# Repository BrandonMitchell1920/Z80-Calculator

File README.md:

# Z80 Calculator

This is a simple Z80 based calculator.  I have been doing various electronics projects
designed by other people and wanted to try making my own.  I figured a calculator
using the Z80 microprocessor would be a good choice as I had several of them on
hand and could reference other projects if needed.

## Features

The Z80 Caclulator has:

* 8K of RAM
* 8K of ROM
* 2 8-bit inputs (DIP switches)
* 6 push buttons
* Program select switch (software controlled)
* 4 seven segment displays (16-bit output)
* Expansion header for additional RAM or devices
* Blinkenlights!
* 555 timer for variable clock rate (useful for debugging)

Pretty basic, but this was more a learning exercise than anything.  Of the 8K ROM,
only a couple hundred bytes are used.  Combined with the program select switch,
it should be possible to load it up with three other programs.

The answers are displayed in hexadecimal so all operations on two eight bit numbers
would fit on the display.  The following operations are supported:

* Addition
* Subtraction
* Multiplication
* Division
* Greatest common denominator
* Square root

Only integer operations are supported, so division and square root are truncated.

## Programming

The Z80 Calculator has the following memory map:

* ROM: 0x0000 - 0x1FFF
* RAM: 0x2000 - 0x3FFF
* Unused: 0x4000 - 0xFFFF

I/O addresses are the following:

* 7SEG 1: 0x00
* 7SEG 2: 0x01
* 7SEG 3: 0x02
* 7SEG 4: 0x03
* Buttons + Program Select: 0x04
* DIP Switch X: 0x05
* DIP Switch Y: 0x06

The buttons and program select switch are mapped to the following bits of the byte
that you read back from their I/O address:

* SW1: Bits 0 and 1
* SW7: Bit 2
* SW6: Bit 3
* SW5: Bit 4
* SW4: Bit 5
* SW3: Bit 6
* SW2: Bit 7

All inputs are wired up to go high when enabled.  The seven segement displays are
also wired up to go high when a one is written to them.  Only one seven segment
display can be on at any time, and they won't stay on while other calculations
are occuring.  You can see an example of how this works in the provided source code.
There are also predefined values for the addresses and seven segment display values.

The idea with the program select switch was that on boot up, the code would check
what it was set to and jump to a different part of ROM.  However, it could be used
in other ways if multiple programs are not desired.

## BOM

Most of the parts can be had from Mouser except for the Z80 CPU.  Those are easy
enough to find on eBay.  Unicorn Electronics is also a good source for these parts
and is often cheaper than eBay or Mouser.  It might be possible to substitute 74HC
parts for the 74HCT, but I reccomend the latter.  74LS should be fine for any chip
that isn't driving an LED.  To use the 555 timer, you'll need a CMOS Z80.

For getting the PCB, I reccommend JLCPCB.  You can upload the included gerber files
to the site and just use their defaults, though change the color if you want.  Use the
cheapest shipping option (not DHL, FedEx, or UPS).

Component type     | Reference  | Description                                 | Quantity | Notes
------------------ | ---------- | ------------------------------------------- | -------- | --------------------------
PCB                |            | PCB                                         | 1        | JLCPCB, PCBWay
Capacitor          | C1,C16     | 1uF, electrolytic, 2mm lead spacing         | 2        | Could replace with ceramic
Capacitor          | C2,C15     | 10uF, electrolytic, 2mm lead spacing        | 2        | Could replace with ceramic
Capacitor          | C3,C4,C5,C6,C7,C8,C9,C10,C11,C12,C13,C14,C17 | 0.1uF, ceramic, 5mm lead spacing        | 13       |
LED                | D1,D2,D3,D4,D5,D6,D7,D8,D9,D10,D11,D12,D13,D14,D15,D16,D17,D18,D19,D20,D21,D22,D23,D24,D25,D26,D27  | 3mm lead spacing        | 27       | Consider mixing up the colors
Connector          | J1         | Barrel jack, 2.1mm                          | 1        |
Connector          | J2         | 2x20 shrouded pin header                    | 1        | Optional, used for expansion header
Connector          | JP1        | 1x3 pin header                              | 1        |
Resistor           | R1,R3,R4   | 2K ohm                                      | 3        |
Resistor           | R2         | 1K ohm                                      | 1        |
Resistor           | R5         | 22K ohm                                     | 1        |
Resistor Network   | RN1,RN4,RN5,RN9 | 10k ohm, 9 pin bussed                  | 4        |
Resistor Network   | RN2,RN3    | 470 ohm, 8 pin isolated                     | 2        | Could use normal resistors and bend leads
Resistor Network   | RN6,RN7,RN8| 2k ohm, 9 pin bussed                        | 3        |
Potentiometer      | RV1        | 50k ohm                                     | 1        |
Switch             | SW1        | DIP Switch 2x                               | 1        |
Switch             | SW2,SW3,SW4,SW5,SW6,SW7,SW8 | 6mm pushbutton             | 7        |
Switch             | SW9,SW10   | DIP Switch 8x                               | 2        |
IC                 | U1         | NE555P                                      | 1        | Other manufacturers are fine
IC                 | U2,U4,U11,U14,U15,U16,U17 | 74HCT245                     | 7        |
IC                 | U3         | Z80, CMOS, 4MHz                             | 1        |
IC                 | U5,U9      | 74HCT138                                    | 2        |
IC                 | U6         | 28C64 EEPROM                                | 1        | Can use 27C64
IC                 | U7,U10,U12,U13 | Seven segment, common cathode           | 4        | 
IC                 | U8         | 6264 RAM                                    | 1        | 
Oscillator         | Y1         | 4 MHz                                       | 1        | Could use a slower one or a faster one if the CPU supports higher speeds

## Building Firmware

I used RASM to assemble this.  Other assemblers would probably work, but the assembler 
directives may need to change.  Use the command "rasm_w64.exe -ob out.bin main.asm" to assemble.

## Misc

I wrote up a little post to my [blog](https://branmitc.blogspot.com/2026/09/homebrew-z80-computer.html) about designing and building this computer, if you
are interested.

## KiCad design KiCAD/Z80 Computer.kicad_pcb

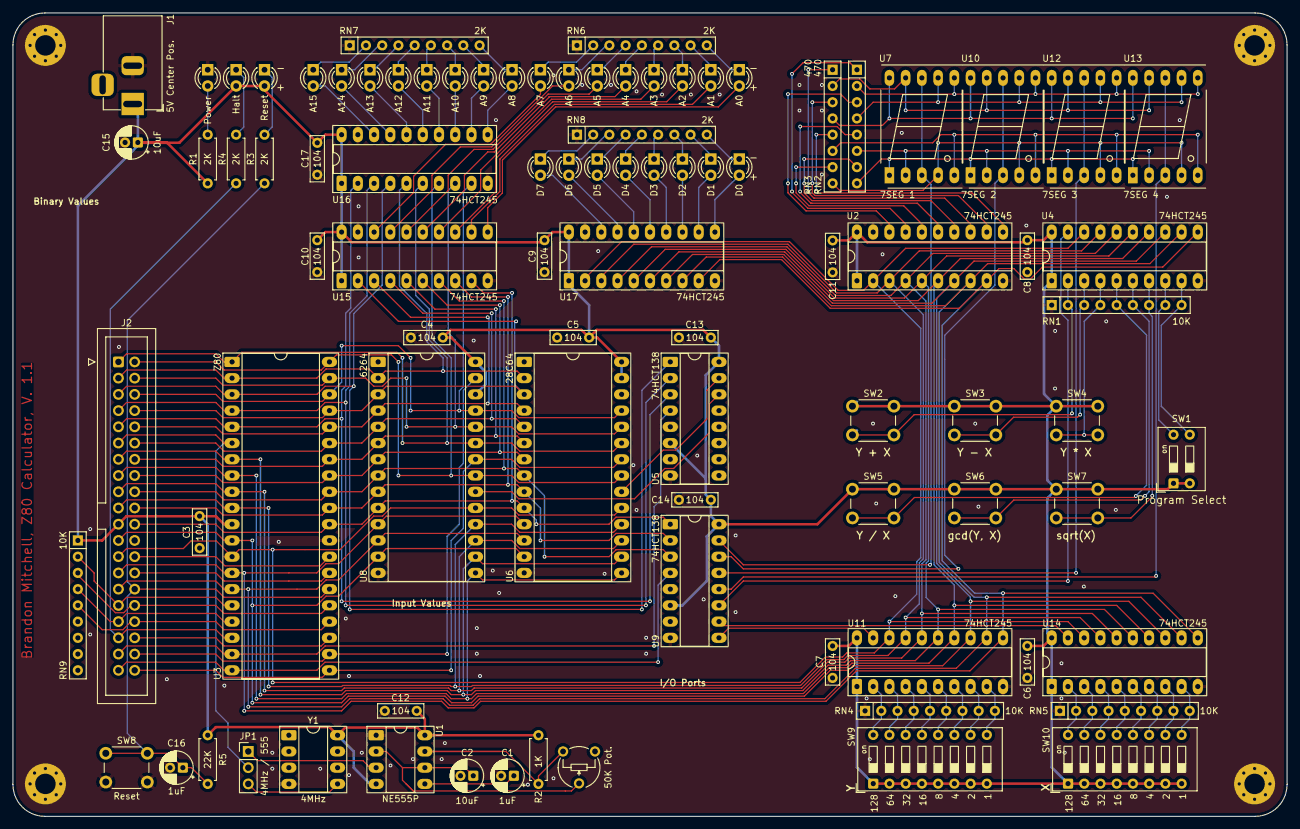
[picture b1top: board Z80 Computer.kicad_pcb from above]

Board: 2 copper layers, 199.4 x 125.7 mm, 94 parts (0 on the bottom side), 145 nets.

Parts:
50K Pot.: 50K; Potentiometer_Piher_PT-6-V_Vertical
A0, A1, A2, A3, A4, A5, A6, A7, A8, A9, A10, A11, A12, A13, A14, A15: LED; LED_D3.0mm
C1, C16: 1uF; CP_Radial_D5.0mm_P2.00mm
C2, C15: 10uF; CP_Radial_D5.0mm_P2.00mm
C3, C4, C5, C6, C7, C8, C11, C12, C13, C14, C17: 0.1uF; C_Rect_L7.0mm_W2.0mm_P5.00mm
C9, C10: 104; C_Rect_L7.0mm_W2.0mm_P5.00mm
D0, D1, D2, D3, D4, D5, D6, D7: LED; LED_D3.0mm
H1, H2, H3, H4: MountingHole_Pad; MountingHole_3.2mm_M3_Pad_Via
Halt: LED; LED_D3.0mm
J1: 5V Center Pos.; BarrelJack_Horizontal
J2: 2x20 Shrouded Header; IDC-Header_2x20_P2.54mm_Vertical_Alt
JP1: 4MHz / 555; PinHeader_1x03_P2.54mm_Vertical
Power: LED; LED_D3.0mm
R1, R3, R4: 2K; R_Axial_DIN0207_L6.3mm_D2.5mm_P7.62mm_Horizontal
R2: 1K; R_Axial_DIN0207_L6.3mm_D2.5mm_P7.62mm_Horizontal
R5: 22K; R_Axial_DIN0207_L6.3mm_D2.5mm_P7.62mm_Horizontal
RN1, RN4, RN5, RN9: 10K; R_Array_SIP9
RN2, RN3: 100 Isolated Network; R_Array_SIP8
RN6, RN7, RN8: 2K; R_Array_SIP9
Reset: LED; LED_D3.0mm
SW1: Program Select; SW_DIP_SPSTx02_Slide_9.78x7.26mm_W7.62mm_P2.54mm
SW2: Y + X; SW_PUSH_6mm
SW3: Y - X; SW_PUSH_6mm
SW4: Y * X; SW_PUSH_6mm
SW5: Y / X; SW_PUSH_6mm
SW6: gcd(Y, X); SW_PUSH_6mm
SW7: sqrt(X); SW_PUSH_6mm
SW8: Reset; SW_PUSH_6mm
SW9, SW10: SW_DIP_x08; SW_DIP_SPSTx08_Slide_9.78x22.5mm_W7.62mm_P2.54mm
U1: NE555P; DIP-8_W7.62mm_Socket_LongPads
U2, U4, U11, U14, U15, U16, U17: 74HCT245; DIP-20_W7.62mm_Socket_LongPads
U3: Z80; DIP-40_W15.24mm_Socket_LongPads
U5, U9: 74HCT138; DIP-16_W7.62mm_Socket_LongPads
U6: 28C64; DIP-28_W15.24mm_Socket_LongPads
U7, U10, U12, U13: 7 Seg CK; 7SegmentLED_LTS6760_LTS6780
U8: 6264; DIP-28_W15.24mm_Socket_LongPads
Y1: 4MHz; DIP-8_W7.62mm_Socket_LongPads

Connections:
/4MHz: JP1.3 (B), Y1.5 (OUT)
/7SEG_1: U7.3 (CC), U7.8 (CC), U9.15 (~Y0)
/7SEG_2: U9.14 (~Y1), U10.3 (CC), U10.8 (CC)
/7SEG_3: U9.13 (~Y2), U12.3 (CC), U12.8 (CC)
/7SEG_4: U9.12 (~Y3), U13.3 (CC), U13.8 (CC)
/7SEG_A: RN2.4 (R2.2), U7.7 (A), U10.7 (A), U12.7 (A), U13.7 (A)
/7SEG_B: RN2.2 (R1.2), U7.6 (B), U10.6 (B), U12.6 (B), U13.6 (B)
/7SEG_C: RN3.8 (R4.2), U7.4 (C), U10.4 (C), U12.4 (C), U13.4 (C)
/7SEG_D: RN2.6 (R3.2), U7.2 (D), U10.2 (D), U12.2 (D), U13.2 (D)
/7SEG_DP: RN3.6 (R3.2), U7.5 (DP), U10.5 (DP), U12.5 (DP), U13.5 (DP)
/7SEG_E: RN2.8 (R4.2), U7.1 (E), U10.1 (E), U12.1 (E), U13.1 (E)
/7SEG_F: RN3.2 (R1.2), U7.9 (F), U10.9 (F), U12.9 (F), U13.9 (F)
/7SEG_G: RN3.4 (R2.2), U7.10 (G), U10.10 (G), U12.10 (G), U13.10 (G)
/555 Out: JP1.1 (A), U1.3 (Q)
/A0: J2.30, U3.30 (A_{0}), U6.10 (A0), U8.10 (A0), U9.1 (A0), U15.9 (A7)
/A1: J2.31, U3.31 (A_{1}), U6.9 (A1), U8.9 (A1), U9.2 (A1), U15.8 (A6)
/A2: J2.32, U3.32 (A_{2}), U6.8 (A2), U8.8 (A2), U9.3 (A2), U15.7 (A5)
/A3: J2.33, U3.33 (A_{3}), U6.7 (A3), U8.7 (A3), U15.6 (A4)
/A4: J2.34, U3.34 (A_{4}), U6.6 (A4), U8.6 (A4), U15.5 (A3)
/A5: J2.35, U3.35 (A_{5}), U6.5 (A5), U8.5 (A5), U15.4 (A2)
/A6: J2.36, U3.36 (A_{6}), U6.4 (A6), U8.4 (A6), U15.3 (A1)
/A7: J2.37, U3.37 (A_{7}), U6.3 (A7), U8.3 (A7), U15.2 (A0)
/A8: J2.38, U3.38 (A_{8}), U6.25 (A8), U8.25 (A8), U16.9 (A7)
/A9: J2.39, U3.39 (A_{9}), U6.24 (A9), U8.24 (A9), U16.8 (A6)
/A10: J2.40, U3.40 (A_{10}), U6.21 (A10), U8.21 (A10), U16.7 (A5)
/A11: J2.1, U3.1 (A_{11}), U6.23 (A11), U8.23 (A11), U16.6 (A4)
/A12: J2.2, U3.2 (A_{12}), U6.2 (A12), U8.2 (A12), U16.5 (A3)
/A13: J2.3, U3.3 (A_{13}), U5.1 (A0), U16.4 (A2)
/A14: J2.4, U3.4 (A_{14}), U5.2 (A1), U16.3 (A1)
/A15: J2.5, U3.5 (A_{15}), U5.3 (A2), U16.2 (A0)
/B0: RN2.3 (R2.1), U2.18 (B0)
/B1: RN2.1 (R1.1), U2.17 (B1)
/B2: RN3.7 (R4.1), U2.16 (B2)
/B3: RN2.5 (R3.1), U2.15 (B3)
/B4: RN2.7 (R4.1), U2.14 (B4)
/B5: RN3.1 (R1.1), U2.13 (B5)
/B6: RN3.3 (R2.1), U2.12 (B6)
/B7: RN3.5 (R3.1), U2.11 (B7)
/BSAK: J2.23, U3.23 (~BUSACK)
/BSRQ: J2.25, RN9.3 (R2), U3.25 (~BUSREQ)
/BTN_0: RN1.2 (R1), SW2.2, U4.2 (A0)
/BTN_1: RN1.3 (R2), SW3.2, U4.3 (A1)
/BTN_2: RN1.4 (R3), SW4.2, U4.4 (A2)
/BTN_3: RN1.5 (R4), SW5.2, U4.5 (A3)
/BTN_4: RN1.6 (R5), SW6.2, U4.6 (A4)
/BTN_5: RN1.7 (R6), SW7.2, U4.7 (A5)
/BTN_CS: U4.19 (CE), U9.11 (~Y4)
/CLK: J2.6, JP1.2 (C), U3.6 (CLK)
/D0: J2.14, U2.9 (A7), U3.14 (D_{0}), U4.11 (B7), U6.11 (I/O0), U8.11 (I/O0), U11.11 (B7), U14.11 (B7), U17.9 (A7)
/D1: J2.15, U2.8 (A6), U3.15 (D_{1}), U4.12 (B6), U6.12 (I/O1), U8.12 (I/O1), U11.12 (B6), U14.12 (B6), U17.8 (A6)
/D2: J2.12, U2.7 (A5), U3.12 (D_{2}), U4.13 (B5), U6.13 (I/O2), U8.13 (I/O2), U11.13 (B5), U14.13 (B5), U17.7 (A5)
/D3: J2.8, U2.6 (A4), U3.8 (D_{3}), U4.14 (B4), U6.15 (I/O3), U8.15 (I/O3), U11.14 (B4), U14.14 (B4), U17.6 (A4)
/D4: J2.7, U2.5 (A3), U3.7 (D_{4}), U4.15 (B3), U6.16 (I/O4), U8.16 (I/O4), U11.15 (B3), U14.15 (B3), U17.5 (A3)
/D5: J2.9, U2.4 (A2), U3.9 (D_{5}), U4.16 (B2), U6.17 (I/O5), U8.17 (I/O5), U11.16 (B2), U14.16 (B2), U17.4 (A2)
/D6: J2.10, U2.3 (A1), U3.10 (D_{6}), U4.17 (B1), U6.18 (I/O6), U8.18 (I/O6), U11.17 (B1), U14.17 (B1), U17.3 (A1)
/D7: J2.13, U2.2 (A0), U3.13 (D_{7}), U4.18 (B0), U6.19 (I/O7), U8.19 (I/O7), U11.18 (B0), U14.18 (B0), U17.2 (A0)
/HALT: J2.18, R4.1, U3.18 (~HALT)
/INT: J2.16, RN9.2 (R1), U3.16 (~INT)
/IORQ: J2.20, U3.20 (~IORQ), U9.4 (~E0)
/M1: J2.27, U3.27 (~M1)
/MREQ: J2.19, U3.19 (~MREQ), U5.4 (~E0)
/NMI: J2.17, RN9.4 (R3), U3.17 (~NMI)
/RAM_CS: U5.14 (~Y1), U8.20 (~CS1)
/RD: J2.21, U3.21 (~RD), U6.22 (~OE), U8.22 (~OE)
/RFSH: J2.28, U3.28 (~RFSH)
/ROM_CS: U5.15 (~Y0), U6.20 (~CE)
/RSET: C16.1, J2.26, R3.2, R5.2, SW8.1, U3.26 (~RESET)
/SW1_0: RN5.9 (R8), SW10.9, U14.9 (A7)
/SW1_1: RN5.8 (R7), SW10.10, U14.8 (A6)
/SW1_2: RN5.7 (R6), SW10.11, U14.7 (A5)
/SW1_3: RN5.6 (R5), SW10.12, U14.6 (A4)
/SW1_4: RN5.5 (R4), SW10.13, U14.5 (A3)
/SW1_5: RN5.4 (R3), SW10.14, U14.4 (A2)
/SW1_6: RN5.3 (R2), SW10.15, U14.3 (A1)
/SW1_7: RN5.2 (R1), SW10.16, U14.2 (A0)
/SW2_0: RN4.9 (R8), SW9.9, U11.9 (A7)
/SW2_1: RN4.8 (R7), SW9.10, U11.8 (A6)
/SW2_2: RN4.7 (R6), SW9.11, U11.7 (A5)
/SW2_3: RN4.6 (R5), SW9.12, U11.6 (A4)
/SW2_4: RN4.5 (R4), SW9.13, U11.5 (A3)
/SW2_5: RN4.4 (R3), SW9.14, U11.4 (A2)
/SW2_6: RN4.3 (R2), SW9.15, U11.3 (A1)
/SW2_7: RN4.2 (R1), SW9.16, U11.2 (A0)
/SW3_0: RN1.9 (R8), SW1.3, U4.9 (A7)
/SW3_1: RN1.8 (R7), SW1.4, U4.8 (A6)
/SW_1_CS: U9.10 (~Y5), U14.19 (CE)
/SW_2_CS: U9.9 (~Y6), U11.19 (CE)
/WAIT: J2.24, RN9.5 (R4), U3.24 (~WAIT)
/WR: J2.22, U3.22 (~WR), U8.27 (~WE)
GND: C1.2, C2.2, C3.2, C4.2, C5.2, C6.2, C7.2, C8.2, C9.2, C10.2, C11.2, C12.2, C13.2, C14.2, C15.2, C16.2, C17.2, H1.1, H2.1, H3.1, H4.1, J1.2, J2.29, Power.1 (K), RN1.1 (common), RN4.1 (common), RN5.1 (common), RN6.1 (common), RN7.1 (common), RN8.1 (common), SW8.2, U1.1 (GND), U2.10 (GND), U2.19 (CE), U3.29 (GND), U4.10 (GND), U5.5 (~E1), U5.8 (GND), U6.14 (GND), U8.14 (GND), U9.5 (~E1), U9.8 (GND), U11.10 (GND), U14.10 (GND), U15.10 (GND), U15.19 (CE), U16.10 (GND), U16.19 (CE), U17.10 (GND), U17.19 (CE), Y1.4 (GND)
unnamed: Power.2 (A), R1.1
unnamed: R3.1, Reset.1 (K)
unnamed: Halt.1 (K), R4.2
unnamed: A7.2 (A), U15.18 (B0)
unnamed: A7.1 (K), RN6.2 (R1)
unnamed: A6.2 (A), U15.17 (B1)
unnamed: A6.1 (K), RN6.3 (R2)
unnamed: A5.2 (A), U15.16 (B2)
unnamed: A5.1 (K), RN6.4 (R3)
unnamed: A4.2 (A), U15.15 (B3)
unnamed: A4.1 (K), RN6.5 (R4)
unnamed: A3.2 (A), U15.14 (B4)
unnamed: A3.1 (K), RN6.6 (R5)
unnamed: A2.2 (A), U15.13 (B5)
unnamed: A2.1 (K), RN6.7 (R6)
unnamed: A1.2 (A), U15.12 (B6)
unnamed: A1.1 (K), RN6.8 (R7)
unnamed: A0.2 (A), U15.11 (B7)
unnamed: A0.1 (K), RN6.9 (R8)
unnamed: A15.2 (A), U16.18 (B0)
unnamed: A15.1 (K), RN7.2 (R1)
unnamed: A14.2 (A), U16.17 (B1)
unnamed: A14.1 (K), RN7.3 (R2)
unnamed: A13.2 (A), U16.16 (B2)
unnamed: A13.1 (K), RN7.4 (R3)
unnamed: A12.2 (A), U16.15 (B3)
unnamed: A12.1 (K), RN7.5 (R4)
unnamed: A11.2 (A), U16.14 (B4)
unnamed: A11.1 (K), RN7.6 (R5)
unnamed: A10.2 (A), U16.13 (B5)
unnamed: A10.1 (K), RN7.7 (R6)
unnamed: A9.2 (A), U16.12 (B6)
unnamed: A9.1 (K), RN7.8 (R7)
unnamed: A8.2 (A), U16.11 (B7)
unnamed: A8.1 (K), RN7.9 (R8)
unnamed: D7.2 (A), U17.18 (B0)
unnamed: D7.1 (K), RN8.2 (R1)
unnamed: D6.2 (A), U17.17 (B1)
unnamed: D6.1 (K), RN8.3 (R2)
unnamed: D5.2 (A), U17.16 (B2)
unnamed: D5.1 (K), RN8.4 (R3)
unnamed: D4.2 (A), U17.15 (B3)
unnamed: D4.1 (K), RN8.5 (R4)
unnamed: D3.2 (A), U17.14 (B4)
unnamed: D3.1 (K), RN8.6 (R5)
unnamed: D2.2 (A), U17.13 (B5)
unnamed: D2.1 (K), RN8.7 (R6)
unnamed: D1.2 (A), U17.12 (B6)
unnamed: D1.1 (K), RN8.8 (R7)
unnamed: D0.2 (A), U17.11 (B7)
unnamed: D0.1 (K), RN8.9 (R8)
unnamed: C1.1, U1.5 (CV)
unnamed: 50K Pot..1, R2.1, U1.7 (DIS)
unnamed: 50K Pot..2, C2.1, U1.2 (TR), U1.6 (THR)
VCC: C3.1, C4.1, C5.1, C6.1, C7.1, C8.1, C9.1, C10.1, C11.1, C12.1, C13.1, C14.1, C15.1, C17.1, Halt.2 (A), J1.1, J2.11, R1.2, R2.2, R5.1, RN9.1 (common), Reset.2 (A), SW1.1, SW1.2, SW2.1, SW3.1, SW4.1, SW5.1, SW6.1, SW7.1, SW9.1, SW9.2, SW9.3, SW9.4, SW9.5, SW9.6, SW9.7, SW9.8, SW10.1, SW10.2, SW10.3, SW10.4, SW10.5, SW10.6, SW10.7, SW10.8, U1.4 (R), U1.8 (VCC), U2.1 (A->B), U2.20 (VCC), U3.11 (V_{CC}), U4.1 (A->B), U4.20 (VCC), U5.6 (E2), U5.16 (VCC), U6.27 (~WE), U6.28 (VCC), U8.26 (CS2), U8.28 (VCC), U9.6 (E2), U9.16 (VCC), U11.1 (A->B), U11.20 (VCC), U14.1 (A->B), U14.20 (VCC), U15.1 (A->B), U15.20 (VCC), U16.1 (A->B), U16.20 (VCC), U17.1 (A->B), U17.20 (VCC), Y1.8 (Vcc)
